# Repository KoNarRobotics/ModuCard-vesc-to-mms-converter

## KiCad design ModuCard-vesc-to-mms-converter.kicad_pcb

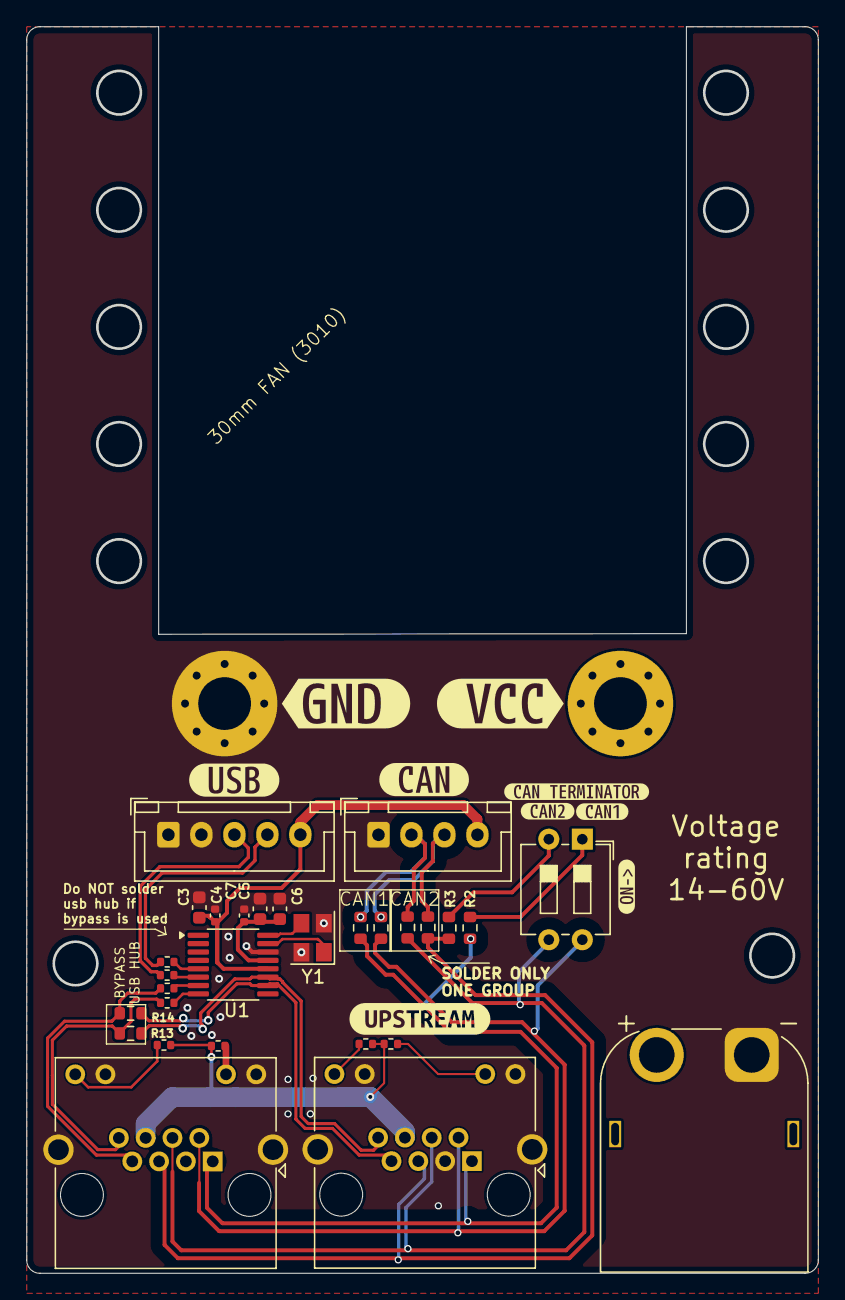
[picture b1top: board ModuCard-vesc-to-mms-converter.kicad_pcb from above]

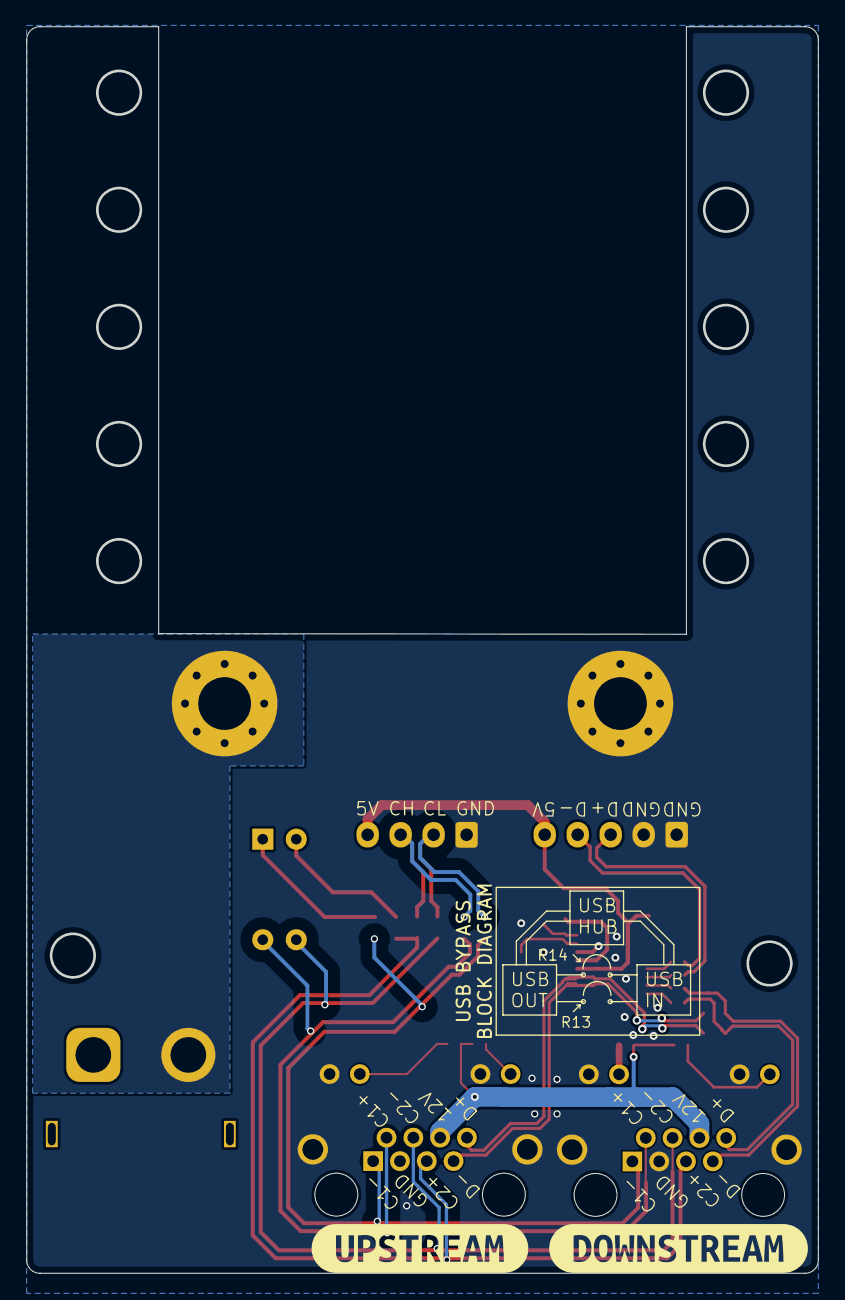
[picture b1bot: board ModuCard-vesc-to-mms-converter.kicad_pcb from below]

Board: 2 copper layers, 59.9 x 94.3 mm, 42 parts (2 on the bottom side), 29 nets.

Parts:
C3, C5: 10u; C_0603_1608Metric
C4, C7: 100n; C_0402_1005Metric
C6: 1u; C_0603_1608Metric
H9: VCC_VESC; MountingHole_4mm_Pad_Via
H10: GND_VESC; MountingHole_4mm_Pad_Via
J1, J2: RJ45_LED_Shielded; RJ45_Amphenol_RJHSE538X
J3: Conn_01x04; JST_XH_B4B-XH-A_1x04_P2.50mm_Vertical
J4: Conn_01x05; JST_XH_B5B-XH-A_1x05_P2.50mm_Vertical
J5: VCC_IN; AMASS_XT60PW-M_1x02_P7.20mm_Horizontal
R1, R4, R17, R18: 1k; R_0402_1005Metric
R2, R3: 120R; R_0603_1608Metric
R5, R6, R7, R8, R13, R14: 0R; R_0603_1608Metric
R9, R10, R11, R12: 22R; R_0402_1005Metric
SW1: SW_DIP_x02; SW_DIP_SPSTx02_Slide_6.7x6.64mm_W7.62mm_P2.54mm_LowProfile
U1: CH334R; QSOP-16_3.9x4.9mm_P0.635mm
Y1: 12Mhz; Crystal_SMD_3225-4Pin_3.2x2.5mm
kibuzzard-68D8378B: G***; kibuzzard-68D8378B
kibuzzard-68D83794: G***; kibuzzard-68D83794
kibuzzard-674E462A: G***; kibuzzard-674E462A
kibuzzard-674E4620: G***; kibuzzard-674E4620
kibuzzard-675D9C7D: G***; kibuzzard-675D9C7D
kibuzzard-675D9C67: G***; kibuzzard-675D9C67
kibuzzard-675D9C73: G***; kibuzzard-675D9C73
kibuzzard-675D9CCD: G***; kibuzzard-675D9CCD
kibuzzard-673147F0: G***; kibuzzard-673147F0
kibuzzard-6754762D: G***; kibuzzard-6754762D
kibuzzard-67314807: G***; kibuzzard-67314807

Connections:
+5V: C3.2, C4.2, J3.4, J4.5, U1.12 (V5)
+12V: J1.6, J2.6, R1.1, R4.1, R17.1, R18.1
/CAN/CAN1+: J1.2, J2.2, R6.2, SW1.4
/CAN/CAN1-: J1.1, J2.1, R2.1, R8.2
/CAN/CAN2+: J1.5, J2.5, R3.1, R5.1
/CAN/CAN2-: J1.4, J2.4, R7.1, SW1.3
/CAN/CAN+: J3.3, R5.2, R6.1
/CAN/CAN-: J3.2, R7.2, R8.1
/USB/USB_VESC_D+: J4.3, R10.1
/USB/USB_VESC_D-: J4.4, R9.1
GND: C3.1, C4.1, C5.1, C6.1, C7.1, H10.1, J1.3, J1.9, J1.11, J1.SH, J2.3, J2.9, J2.11, J2.SH, J3.1, J4.1, J4.2, J5.1, U1.14 (GND), Y1.2, Y1.4
unnamed: J1.10, R1.2
unnamed: J1.12, R18.2
unnamed: J2.10, R17.2
unnamed: J2.12, R4.2
unnamed: R2.2, SW1.1
unnamed: R3.2, SW1.2
unnamed: R11.1, U1.7 (DM1)
unnamed: R9.2, U1.5 (DM2)
unnamed: R12.2, U1.8 (DP1)
unnamed: R10.2, U1.6 (DP2)
unnamed: C5.2, C6.2, C7.2, U1.13 (VDD33)
unnamed: U1.16 (XI), Y1.3
unnamed: U1.15 (XO), Y1.1
USB_DOWNSTREAM_D+: J2.8, R12.1, R13.1
USB_DOWNSTREAM_D-: J2.7, R11.2, R14.1
USB_UPSTREAM_D+: J1.8, R13.2, U1.11 (DPU)
USB_UPSTREAM_D-: J1.7, R14.2, U1.10 (DMU)
VCC: H9.1, J5.2

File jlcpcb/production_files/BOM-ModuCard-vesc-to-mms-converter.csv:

Comment,Designator,Footprint,LCSC,Quantity
CH334R,U1,QSOP-16_3.9x4.9mm_P0.635mm,,1
10u,C5,C_0603_1608Metric,,1
SW_DIP_x02,SW1,SW_DIP_SPSTx02_Slide_6.7x6.64mm_W7.62mm_P2.54mm_LowProfile,,1
22R,R11,R_0402_1005Metric,,1
0R,R8,R_0603_1608Metric,,1
120R,R2,R_0603_1608Metric,,1
22R,R12,R_0402_1005Metric,,1
120R,R3,R_0603_1608Metric,,1
Conn_01x05,J4,JST_XH_B5B-XH-A_1x05_P2.50mm_Vertical,,1
VCC_IN,J5,AMASS_XT60PW-M_1x02_P7.20mm_Horizontal,,1
12Mhz,Y1,Crystal_SMD_3225-4Pin_3.2x2.5mm,,1
22R,R9,R_0402_1005Metric,,1
0R,R6,R_0603_1608Metric,,1
1u,C6,C_0603_1608Metric,,1
10u,C3,C_0603_1608Metric,,1
100n,C4,C_0402_1005Metric,,1
100n,C7,C_0402_1005Metric,,1
0R,R7,R_0603_1608Metric,,1
0R,R5,R_0603_1608Metric,,1
22R,R10,R_0402_1005Metric,,1
0R,R13,R_0603_1608Metric,,1
RJ45_LED_Shielded,J1,RJ45_Amphenol_RJHSE538X,,1
RJ45_LED_Shielded,J2,RJ45_Amphenol_RJHSE538X,,1
0R,R14,R_0603_1608Metric,,1
1k,R17,R_0402_1005Metric,,1
1k,R18,R_0402_1005Metric,,1
Conn_01x04,J3,JST_XH_B4B-XH-A_1x04_P2.50mm_Vertical,,1
1k,R1,R_0402_1005Metric,,1
1k,R4,R_0402_1005Metric,,1

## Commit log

2025-09-27 aded readme
